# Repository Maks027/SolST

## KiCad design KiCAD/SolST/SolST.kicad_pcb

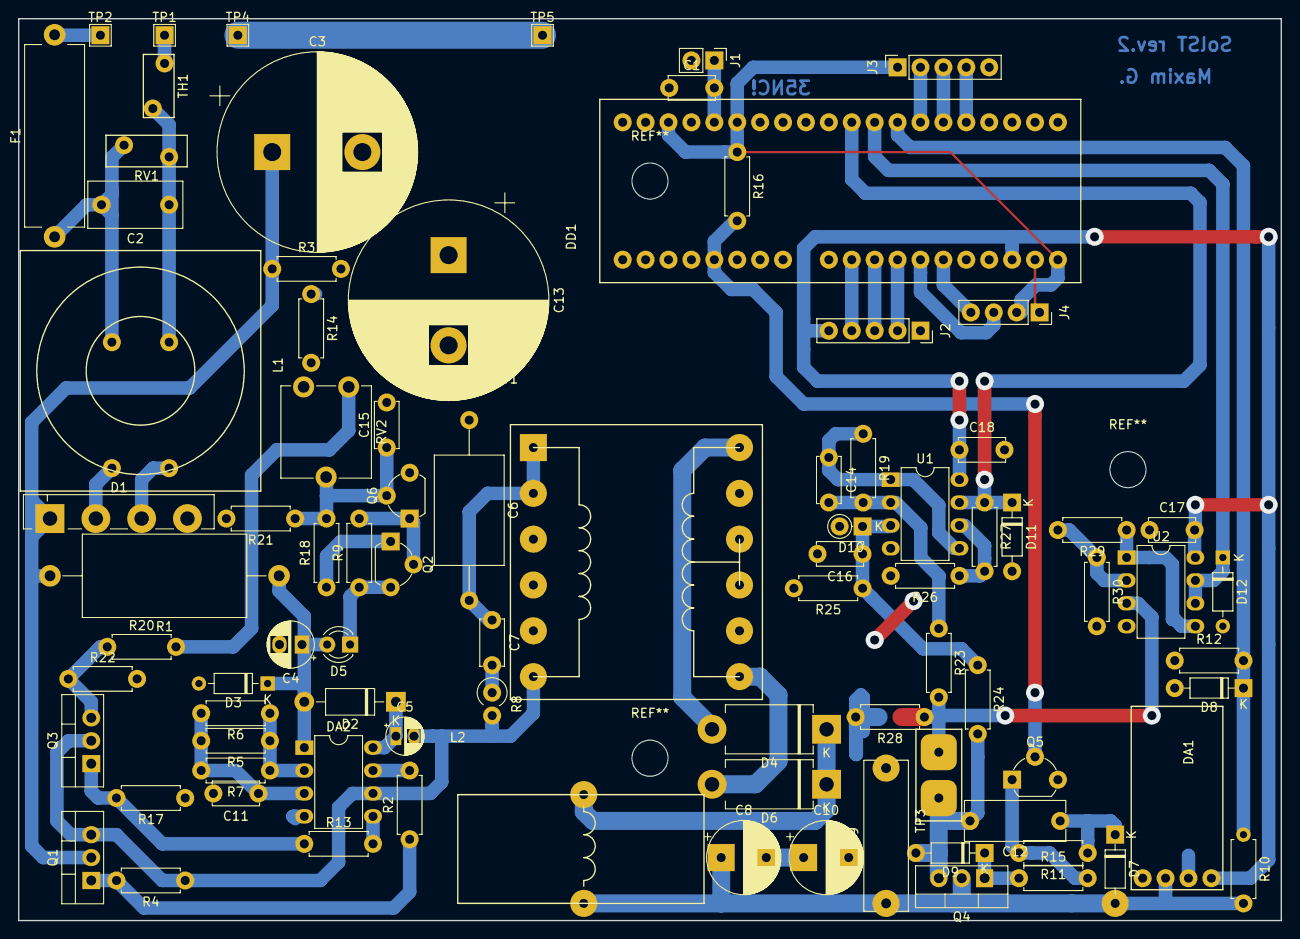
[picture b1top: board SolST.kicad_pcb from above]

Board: 2 copper layers, 140.0 x 100.0 mm, 87 parts (0 on the bottom side), 59 nets.

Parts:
C1: 100N; C_Disc_D5.0mm_W2.5mm_P5.00mm
C2: 47n; C_Rect_L10.3mm_W5.0mm_P7.50mm_MKS4
C3, C13: 330uF,200V; CP_Radial_D22.0mm_P10.00mm_SnapIn
C4: 10uF; CP_Radial_D5.0mm_P2.50mm
C5: 2.2uF; CP_Radial_D4.0mm_P2.00mm
C6: 1uF,250V; C_Axial_L12.0mm_D7.5mm_P20.00mm_Horizontal
C7: 2.2, 1.2kV; C_Disc_D5.0mm_W2.5mm_P5.00mm
C8, C10: 680uF,16V; CP_Radial_D8.0mm_P5.00mm
C9: 1.5uF; C_Rect_L16.5mm_W4.7mm_P15.00mm_MKT
C11: 2.2nF; C_Disc_D5.0mm_W2.5mm_P5.00mm
C12: 470n; C_Rect_L11.0mm_W4.3mm_P10.00mm_MKT
C14, C16: 10n; C_Disc_D5.0mm_W2.5mm_P5.00mm
C15: 10nF; C_Disc_D5.0mm_W2.5mm_P5.00mm
C17, C18: 100nF; C_Disc_D5.0mm_W2.5mm_P5.00mm
D1: GBU4D; Diode_Bridge_Vishay_GBL
D2: FR107; D_DO-41_SOD81_P10.16mm_Horizontal
D3, D9: 15V; D_DO-35_SOD27_P7.62mm_Horizontal
D4, D6: FR302; D_DO-201AD_P12.70mm_Horizontal
D5: LED; LED_D3.0mm
D7: 1N4148; D_DO-35_SOD27_P7.62mm_Horizontal
D8, D11, D12: 3V3; D_DO-35_SOD27_P7.62mm_Horizontal
D10: 5V1; D_DO-35_SOD27_P2.54mm_Vertical_KathodeUp
DA1: DC-DC
DA2: IR2153; DIP-8_W7.62mm
DD1: BluePill
F1: Fuse; R_Axial_Power_L20.0mm_W6.4mm_P22.40mm
J1: But_Conn; PinHeader_1x02_P2.54mm_Vertical
J2: Led_Conn; PinSocket_1x05_P2.54mm_Vertical
J3: Enc_Conn; PinSocket_1x05_P2.54mm_Vertical
J4: Disp_Conn; PinSocket_1x04_P2.54mm_Vertical
L1: L_Core_Ferrite_Coupled; ferrite_ring_filter
L2: 50uH; out_inductor
Q1, Q3: IRF740; TO-220-3_Vertical
Q2: KT209; TO-92L_Wide
Q4: IRFZ44N; TO-220-3_Vertical
Q5: BC337; TO-92_Wide
Q6: KT3102; TO-92L_Wide
R1: 18K; R_Axial_DIN0918_L18.0mm_D9.0mm_P25.40mm_Horizontal
R2, R13: 30R; R_Axial_DIN0207_L6.3mm_D2.5mm_P7.62mm_Horizontal
R3, R14: 62K; R_Axial_DIN0207_L6.3mm_D2.5mm_P7.62mm_Horizontal
R4, R11, R17, R30: 1K; R_Axial_DIN0207_L6.3mm_D2.5mm_P7.62mm_Horizontal
R5, R6: NC; R_Axial_DIN0207_L6.3mm_D2.5mm_P7.62mm_Horizontal
R7, R9, R16, R21: 10K; R_Axial_DIN0207_L6.3mm_D2.5mm_P7.62mm_Horizontal
R8: 100R; R_Axial_DIN0309_L9.0mm_D3.2mm_P2.54mm_Vertical
R10: 33K; R_Axial_DIN0207_L6.3mm_D2.5mm_P7.62mm_Horizontal
R12: 4.7K; R_Axial_DIN0207_L6.3mm_D2.5mm_P7.62mm_Horizontal
R15: 2.2K; R_Axial_DIN0207_L6.3mm_D2.5mm_P7.62mm_Horizontal
R18, R20: 100R; R_Axial_DIN0207_L6.3mm_D2.5mm_P7.62mm_Horizontal
R19, R25: 150K; R_Axial_DIN0207_L6.3mm_D2.5mm_P7.62mm_Horizontal
R22: 0.1R; R_Axial_DIN0207_L6.3mm_D2.5mm_P7.62mm_Horizontal
R23, R24: 15K; R_Axial_DIN0207_L6.3mm_D2.5mm_P7.62mm_Horizontal
R26: 6.2K; R_Axial_DIN0207_L6.3mm_D2.5mm_P7.62mm_Horizontal
R27: 100K; R_Axial_DIN0207_L6.3mm_D2.5mm_P7.62mm_Horizontal
R28: 0.05R; R_Axial_DIN0207_L6.3mm_D2.5mm_P7.62mm_Horizontal
R29: 20K; R_Axial_DIN0207_L6.3mm_D2.5mm_P7.62mm_Horizontal
RV1: Varistor; RV_Disc_D9mm_W3.5mm_P5mm
RV2: R_POT; Potentiometer_ACP_CA9-V10_Vertical
T1: Transformer_1P_2S; EI-33
TH1: Thermistor_NTC; RV_Disc_D7mm_W3.4mm_P5mm
TP1: L; TestPoint_THTPad_2.0x2.0mm_Drill1.0mm
TP2: N; TestPoint_THTPad_2.0x2.0mm_Drill1.0mm
TP3: Termoelement; S_Con
TP4: EARTH; TestPoint_THTPad_2.0x2.0mm_Drill1.0mm
TP5: EARTH_I; TestPoint_THTPad_2.0x2.0mm_Drill1.0mm
U1, U2: LM358; DIP-8_W7.62mm

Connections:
+3V3: DD1.20, DD1.35, DD1.38, J3.1, J4.2, R16.1
+5V: C17.2, C18.1, DA1.4, DD1.18, J2.5, U1.8, U2.8
+24V: C8.1, C9.1, D7.2, DA1.2, L2.2, Q4.2, R10.2
/+310V: C3.1, D1.1, Q1.2, R1.2, R3.1
/BOOST: C5.1, D2.1, DA2.8
/EARTH: TP4.1, TP5.1
/GND_SH: Q3.3, R20.1, R22.1
/HB_M: C5.2, DA2.6, Q1.3, Q3.2, R4.1, R8.2, T1.2
/HO: DA2.7, R2.2
/L: TH1.2, TP1.1
/LO: DA2.5, R13.2
/N: F1.2, TP2.1
/SCL: DD1.14, J4.3
/SDA: DD1.15, J4.4
GND: C4.2, C11.2, C13.2, C15.2, D1.4, D3.2, DA2.4, Q6.3, R14.2, R17.1, R21.2, R22.2, RV2.1
GNDD: C1.1, C9.2, C10.2, C16.2, C17.1, C18.2, D8.2, D10.2, D11.2, D12.2, DA1.3, DD1.19, DD1.39, DD1.40, J1.2, J2.1, J3.5, J4.1, Q5.3, R12.1, R25.2, R26.2, R28.2, R30.2, T1.4, T1.5, U1.4, U2.4
I_ADC: D12.1, DD1.29, U2.6, U2.7
unnamed: C1.2, DD1.36, J1.1
unnamed: C2.1, L1.1, RV1.2, TH1.1
unnamed: C2.2, F1.1, L1.3, RV1.1
unnamed: C4.1, D2.2, D3.1, D5.2, DA2.1, R1.1
unnamed: C6.2, C7.1, T1.1
unnamed: C7.2, R8.1
unnamed: C8.2, C10.1
unnamed: C11.1, DA2.3, R5.2, R6.2, R7.2
unnamed: C12.1, D7.1, R11.1
unnamed: C12.2, D9.2, Q4.3, R24.2, TP3.1
unnamed: C3.2, C6.1, C13.1, R3.2, R14.1
unnamed: C14.1, R19.1, U1.1, U1.5
unnamed: C14.2, R19.2, R23.1, U1.2
unnamed: C15.1, Q6.2, R18.2, R21.1, RV2.2
unnamed: C16.1, D10.1, R24.1, R25.1, U1.3
unnamed: D1.2, L1.4
unnamed: D1.3, L1.2
unnamed: D4.1, D6.1, L2.1
unnamed: D4.2, T1.3
unnamed: D5.1, Q2.3, R9.1
unnamed: D6.2, T1.6
unnamed: D9.1, Q4.1, R15.1
unnamed: DA2.2, R5.1, R6.1, R7.1
unnamed: DD1.11, J2.4
unnamed: DD1.12, J2.3
unnamed: DD1.13, J2.2
unnamed: DD1.25, J3.4
unnamed: DD1.26, J3.3
unnamed: DD1.27, J3.2
unnamed: Q1.1, R2.1, R4.2
unnamed: Q2.1, R18.1
unnamed: Q2.2, Q6.1, R9.2
unnamed: Q3.1, R13.1, R17.2
unnamed: Q5.1, R11.2, R15.2
unnamed: R20.2, RV2.3
unnamed: R23.2, R28.1, TP3.2, U2.3
unnamed: R26.1, R27.2, U1.6
unnamed: R29.1, U2.1, U2.5
unnamed: R29.2, R30.1, U2.2
PWM_OUT: DD1.5, Q5.2, R16.2
T_ADC: D11.1, DD1.30, R27.1, U1.7
U_ADC: D8.1, DD1.28, R10.1, R12.2
